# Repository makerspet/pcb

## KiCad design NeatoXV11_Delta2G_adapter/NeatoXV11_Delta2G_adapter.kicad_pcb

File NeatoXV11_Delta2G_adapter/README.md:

# Adapter PCB for LDS02RR laser distance scanner

Connect Neato XV-11/Botvac or Delta-2G LDS to Arduino to capture laser distance data.

This PCB implements PWM motor control for Neato XV/Botvac and Delta-2G LDS. Find
sample Arduino ESP32 firmware code [here](https://github.com/kaiaai/LDS02RR_ESP32)
and Arduino LDS library [here](https://github.com/kaiaai/LDS).

## Files
- [schematic PDF](output/NeatoXV11_Delta2G_adapter_schematic.pdf)
- [BoM .CSV](output/NeatoXV11_Delta2G_adapter_BOM.csv), [BoM .XML](output/NeatoXV11_Delta2G_adapter_BOM.xml)
- [Gerber .ZIP](output/NeatoXV11_Delta2G_adapter_gerber.zip)
- [3D model .STEP](output/NeatoXV11_Delta2G_adapter.step)
- KiCAD schematic, layout - in this folder

## Top

## Bottom

# Change log

## v0.3.0
- added Delta-2G connector

## v0.2.0
- added a bypass capacitor

## v0.1.0
- initial prototype
- optional LM2596 voltage regulator module provides 3.3V to motor

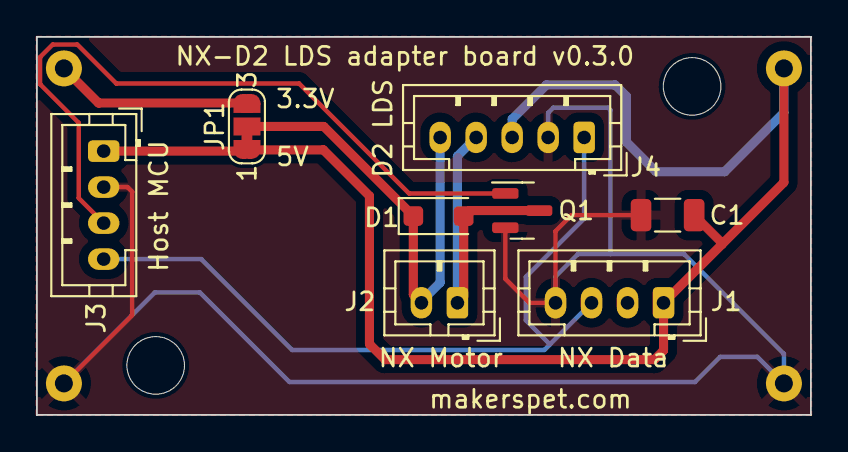
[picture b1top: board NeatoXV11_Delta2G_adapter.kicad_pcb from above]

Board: 2 copper layers, 43.0 x 21.0 mm, 11 parts (1 on the bottom side), 7 nets.

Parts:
C1: 100uF; C_1206_3216Metric
D1: FS26; D_SOD-123F
H1, H2: MountingHole; MountingHole_3.2mm_M3
J1: JST PH2.0 B4B Vert; JST_PH_B4B-PH-K_1x04_P2.00mm_Vertical
J2: JST PH2.0 B2B Vert; JST_PH_B2B-PH-K_1x02_P2.00mm_Vertical
J3: JST PH B4B Vert; JST_PH_B4B-PH-K_1x04_P2.00mm_Vertical
J4: JST PH2.0 B5B Vert; JST_PH_B5B-PH-K_1x05_P2.00mm_Vertical
JP1: SolderJumper_3_Bridged12; SolderJumper-3_P1.3mm_Bridged12_RoundedPad1.0x1.5mm_NumberL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
Q1: AS2302; SOT-23
U1: DNP LM2596; LM2596 Module

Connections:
+3.3V: JP1.3 (B), U1.3 (VOUT+)
+5V: C1.1, J1.1, J3.1, J4.3, JP1.1 (A), U1.4 (VIN+)
/MOT+: D1.1 (K), J2.2, J4.5, JP1.2 (C)
/MOT-: D1.2 (A), J2.1, J4.4, Q1.3 (D)
/MOT_EN: J3.3, Q1.1 (G)
/TX: J1.3, J3.4, J4.1
GND: C1.2, J1.4, J3.2, J4.2, Q1.2 (S), U1.1 (VIN-), U1.2 (VOUT-)

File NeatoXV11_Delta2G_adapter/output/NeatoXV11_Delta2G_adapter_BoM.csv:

"Source:","C:\Users\ilya\git\pcb\NeatoXV11_Delta2G_adapter\NeatoXV11_Delta2G_adapter.kicad_sch"
"Date:","1/31/2024 10:54:29 PM"
"Tool:","Eeschema 7.0.9"
"Generator:","C:\Program Files\KiCad\7.0\bin\scripting\plugins/bom_csv_grouped_by_value_with_fp.py"
"Component Count:","8"
"Ref","Qnty","Value","Cmp name","Footprint","Description","Vendor","DNP"
"C1","1","100uF","C","Capacitor_SMD:C_1206_3216Metric","Unpolarized capacitor","",""
"D1","1","FS26","D_Schottky","Diode_SMD:D_SOD-123F","Schottky diode","",""
"J1","1","JST PH2.0 B4B Vert","Conn_01x04","Connector_JST:JST_PH_B4B-PH-K_1x04_P2.00mm_Vertical","Generic connector, single row, 01x04, script generated (kicad-library-utils/schlib/autogen/connector/)","",""
"J2","1","JST PH2.0 B2B Vert","Conn_01x02","Connector_JST:JST_PH_B2B-PH-K_1x02_P2.00mm_Vertical","Generic connector, single row, 01x02, script generated (kicad-library-utils/schlib/autogen/connector/)","",""
"J3","1","JST PH B4B Vert","Conn_01x04","Connector_JST:JST_PH_B4B-PH-K_1x04_P2.00mm_Vertical","Generic connector, single row, 01x04, script generated (kicad-library-utils/schlib/autogen/connector/)","",""
"J4","1","DNP JST PH2.0 B5B Vert","Conn_01x05","Connector_JST:JST_PH_B5B-PH-K_1x05_P2.00mm_Vertical","Generic connector, single row, 01x05, script generated (kicad-library-utils/schlib/autogen/connector/)","",""
"Q1","1","AS2302","BSS123","Package_TO_SOT_SMD:SOT-23","0.17A Id, 100V Vds, N-Channel MOSFET, SOT-23","",""
"U1","1","DNP LM2596","LM2596 Module","Makerspet:LM2596 Module","DC-DC voltage regulator module","",""
